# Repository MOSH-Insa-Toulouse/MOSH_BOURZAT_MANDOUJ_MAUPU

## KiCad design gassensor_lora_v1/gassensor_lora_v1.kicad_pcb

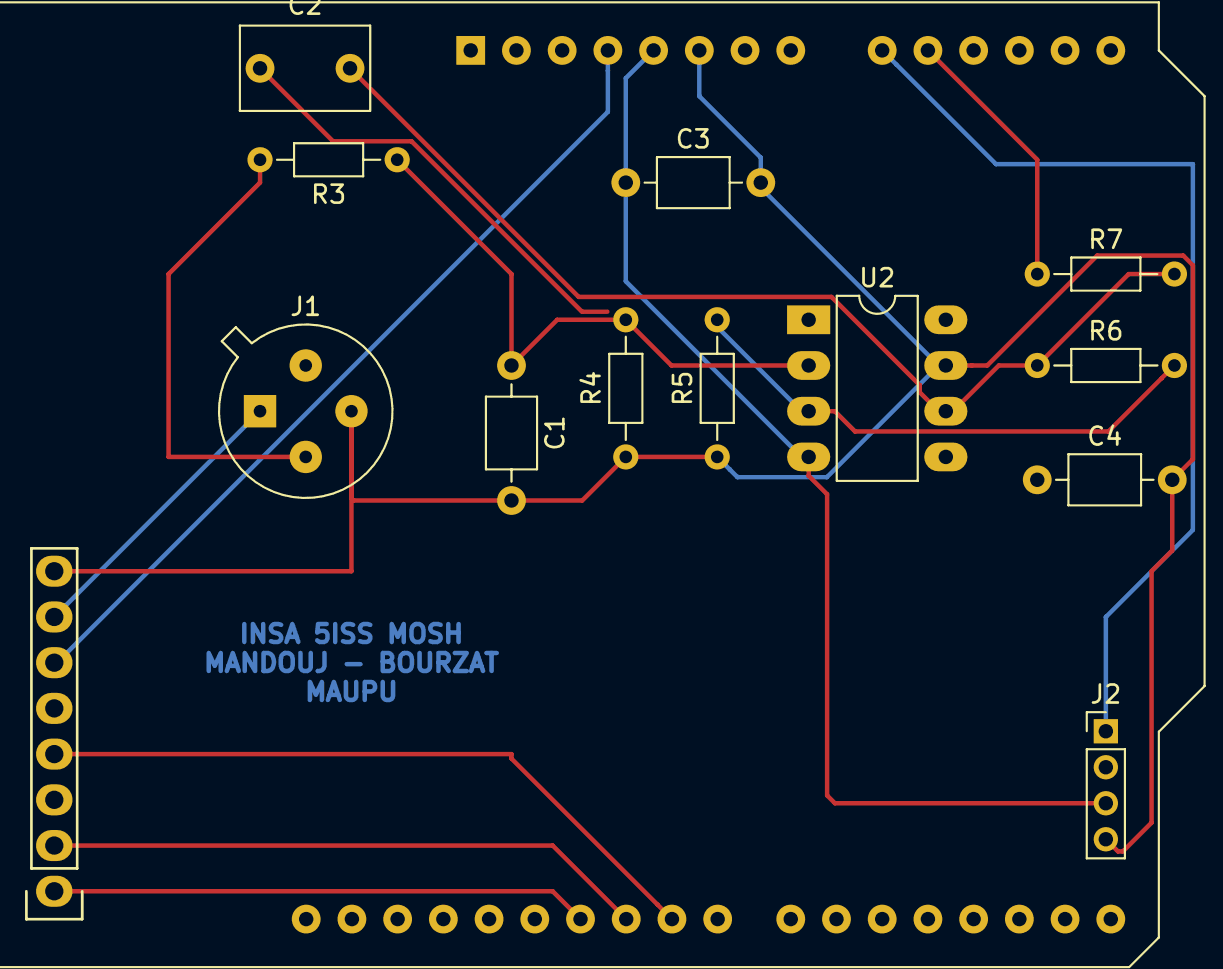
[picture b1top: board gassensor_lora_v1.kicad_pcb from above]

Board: 2 copper layers, 14 parts (0 on the bottom side), 12 nets.

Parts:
A1: Arduino_UNO_R3
C1, C3, C4: 100n; C_Axial_L3.8mm_D2.6mm_P7.50mm_Horizontal
C2: 1µ; C_Rect_L7.0mm_W4.5mm_P5.00mm
J1: Conn_01x04; TO-5-4_1
J2: Conn_01x04; PinHeader_1x04_P2.00mm_Vertical
R3: 10k; R_Axial_DIN0204_L3.6mm_D1.6mm_P7.62mm_Horizontal
R4, R6: 100k; R_Axial_DIN0204_L3.6mm_D1.6mm_P7.62mm_Horizontal
R5, R7: 1k; R_Axial_DIN0204_L3.6mm_D1.6mm_P7.62mm_Horizontal
U1: RN2483A; Socket_Strip_Arduino_1x08
U2: LTC1050; DIP-8_W7.62mm_LongPads

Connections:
+3V3: A1.4, J1.1, U1.6, U1.7
+5V: A1.5, C3.1, J2.3, U2.4
A0: A1.9, J2.1
A1: A1.10, C4.1, R7.1
GND: A1.6, C1.2, C3.2, C4.2, J1.3, J2.4, R4.1, R5.1, U1.8, U2.7
unnamed: C1.1, R3.1, R4.2, U2.2
unnamed: C2.1, R5.2, R6.2, U2.3
unnamed: C2.2, R6.1, R7.2, U2.6
unnamed: J1.2, R3.2
RST: A1.24, U1.4
Rx: A1.25, U1.2
Tx: A1.26, U1.1

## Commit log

2020-01-21 Add kicad files
2020-01-21 Add Arduino file
2020-01-23 add report
